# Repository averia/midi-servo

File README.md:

# midi-servo
arduino with midi in-thru-out to move servomotors

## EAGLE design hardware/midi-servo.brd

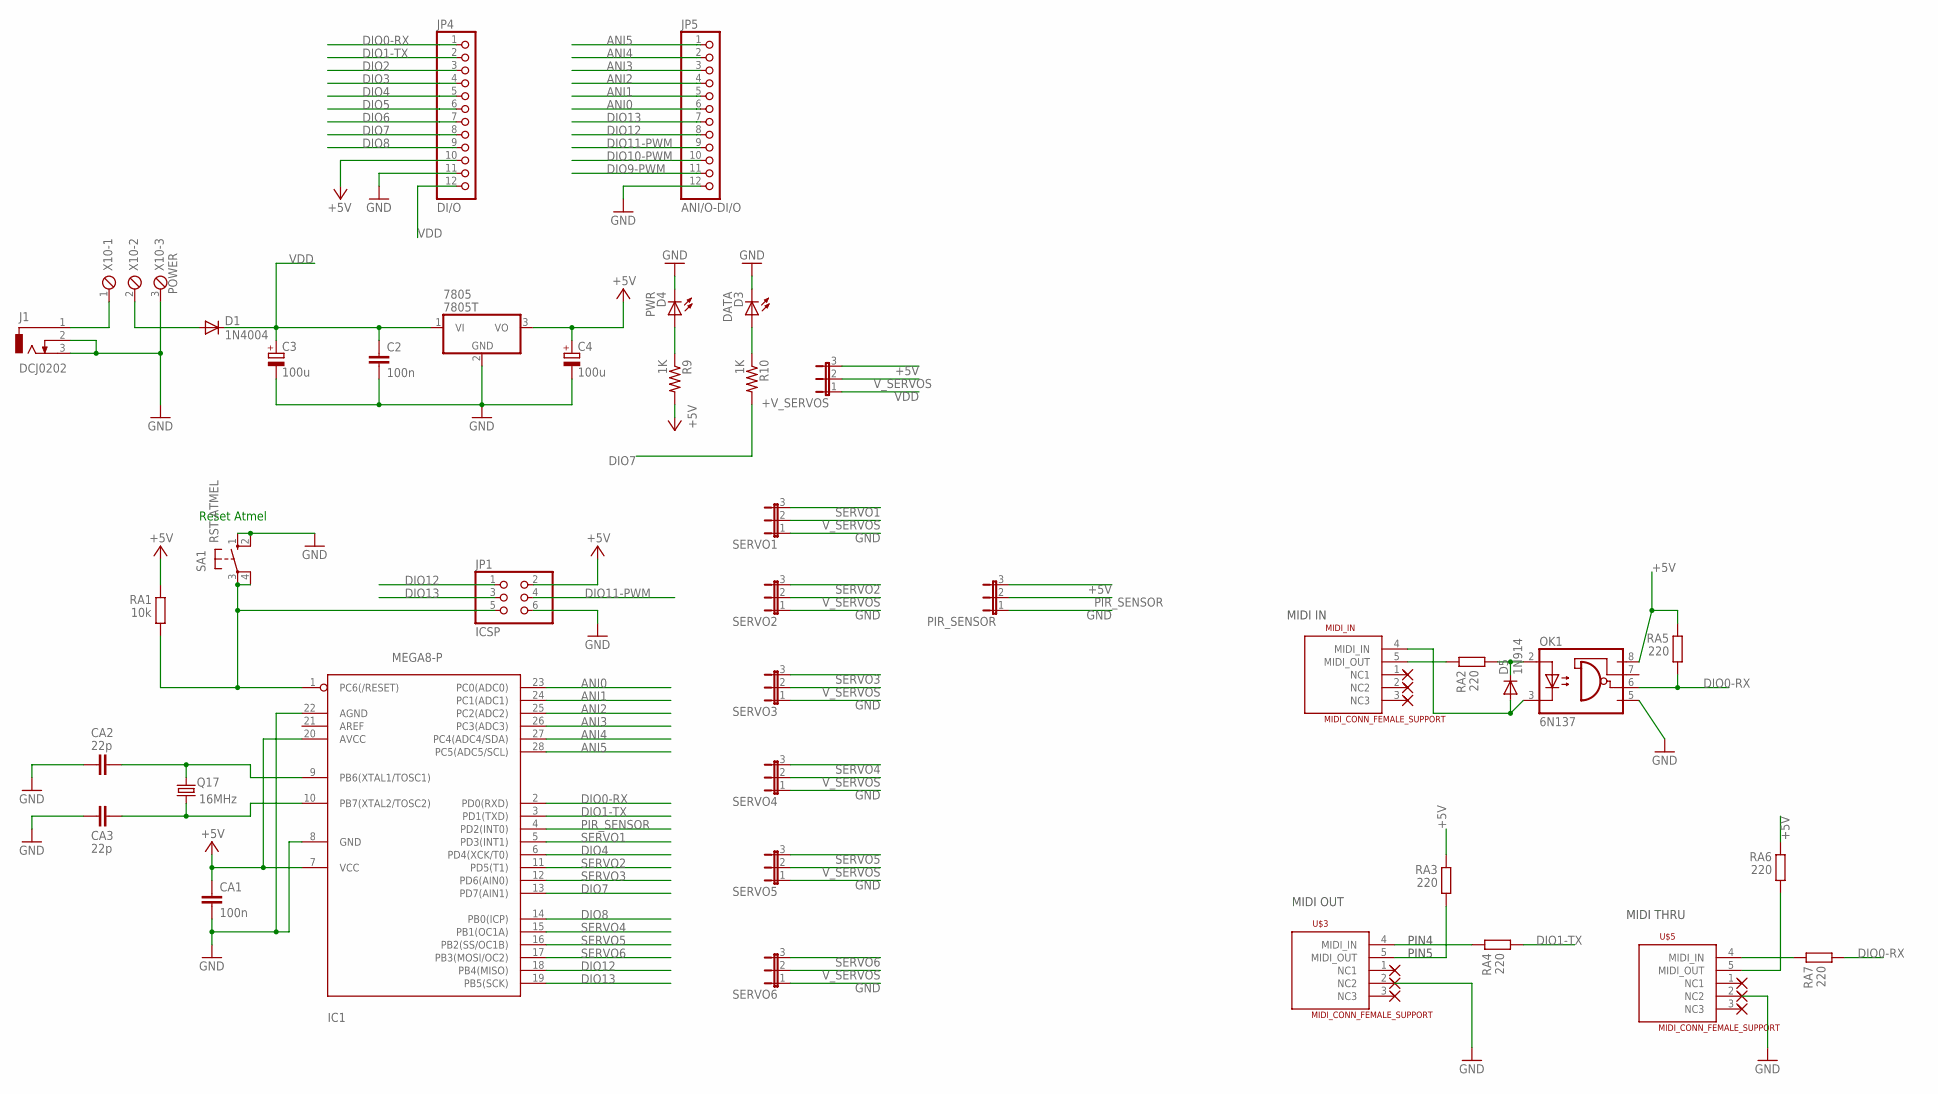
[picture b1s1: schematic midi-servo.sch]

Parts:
7805: 7805T; TO220H
+V_SERVOS: JP2E; JP2
C2: 100n; C050-025X075
C3, C4: 100u; E2,5-7
CA1: 100n; C050-025X075
CA2, CA3: 22p; C050-025X075
D1: 1N4004; DO41-10
D3: DATA; LED4MM
D4: PWR; LED4MM
D5: 1N914; DO34-7
IC1: MEGA8-P; DIL28-3
J1: DCJ0202
JP1: ICSP; 2X03
JP4: DI/O; 1X12
JP5: ANI/O-DI/O; 1X12
MIDI_IN: MIDI_CONN_FEMALE_SUPPORT; DIN_5_FEMALE_SUPPORT
OK1: 6N137; DIL08
PIR_SENSOR: JP2E; JP2
Q17: 16MHz; HC49/S
R9, R10: 1K; 0204/5
RA1: 10k; 0204/5
RA2, RA3, RA4, RA5, RA6, RA7: 220; 0204/5
SA1: RST-ATMEL; B3F-10XX
SERVO1, SERVO2, SERVO3, SERVO4, SERVO5, SERVO6: JP2E; JP2
U$3, U$5: MIDI_CONN_FEMALE_SUPPORT; DIN_5_FEMALE_SUPPORT
X10: POWER; 3POL254

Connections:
56: D5.C, OK1.2 (A), RA2.2
1235: RA3.2, U$3.5 (MIDI_OUT)
+5V: 7805.3 (VO), +V_SERVOS.3, C4.+, CA1.1, IC1.7 (VCC), IC1.20 (AVCC), JP1.2, JP4.10, OK1.8 (VCC), PIR_SENSOR.3, R9.2, RA1.1, RA3.1, RA5.1, RA6.1
ANI0: IC1.23 (PC0(ADC0)), JP5.6
ANI1: IC1.24 (PC1(ADC1)), JP5.5
ANI2: IC1.25 (PC2(ADC2)), JP5.4
ANI3: IC1.26 (PC3(ADC3)), JP5.3
ANI4: IC1.27 (PC4(ADC4/SDA)), JP5.2
ANI5: IC1.28 (PC5(ADC5/SCL)), JP5.1
DIO0-RX: IC1.2 (PD0(RXD)), JP4.1, OK1.6 (VO), RA5.2, RA7.2
DIO1-TX: IC1.3 (PD1(TXD)), JP4.2, RA4.2
DIO2: JP4.3
DIO3: JP4.4
DIO4: IC1.6 (PD4(XCK/T0)), JP4.5
DIO5: JP4.6
DIO6: JP4.7
DIO7: IC1.13 (PD7(AIN1)), JP4.8, R10.2
DIO8: IC1.14 (PB0(ICP)), JP4.9
DIO9-PWM: JP5.11
DIO10-PWM: JP5.10
DIO11-PWM: JP1.4, JP5.9
DIO12: IC1.18 (PB4(MISO)), JP1.1, JP5.8
DIO13: IC1.19 (PB5(SCK)), JP1.3, JP5.7
GND: 7805.2 (GND), C2.2, C3.-, C4.-, CA1.2, CA2.2, CA3.2, D3.A (C), D4.A (C), IC1.8 (GND), IC1.22 (AGND), J1.2, J1.3, JP1.6, JP4.11, JP5.12, OK1.5 (GND), PIR_SENSOR.1, SA1.1 (S), SA1.2 (S1), SERVO1.1, SERVO2.1, SERVO3.1, SERVO4.1, SERVO5.1, SERVO6.1, U$3.2 (NC2), U$5.2 (NC2), X10.3
unnamed: J1.1, X10.1
unnamed: IC1.1 (PC6(/RESET)), JP1.5, RA1.2, SA1.3, SA1.4 (P1)
unnamed: D1.A, X10.2
unnamed: CA2.1, IC1.9 (PB6(XTAL1/TOSC1)), Q17.2
unnamed: CA3.1, IC1.10 (PB7(XTAL2/TOSC2)), Q17.1
unnamed: RA4.1, U$3.4 (MIDI_IN)
unnamed: RA6.2, U$5.5 (MIDI_OUT)
unnamed: RA7.1, U$5.4 (MIDI_IN)
unnamed: MIDI_IN.5 (MIDI_OUT), RA2.1
unnamed: D3.K (A), R10.1
unnamed: D4.K (A), R9.1
PIN5: D5.A, MIDI_IN.4 (MIDI_IN), OK1.3 (C)
PIR_SENSOR: IC1.4 (PD2(INT0)), PIR_SENSOR.2
SERVO1: IC1.5 (PD3(INT1)), SERVO1.3
SERVO2: IC1.11 (PD5(T1)), SERVO2.3
SERVO3: IC1.12 (PD6(AIN0)), SERVO3.3
SERVO4: IC1.15 (PB1(OC1A)), SERVO4.3
SERVO5: IC1.16 (PB2(SS/OC1B)), SERVO5.3
SERVO6: IC1.17 (PB3(MOSI/OC2)), SERVO6.3
VDD: 7805.1 (VI), +V_SERVOS.1, C2.1, C3.+, D1.C, JP4.12
V_SERVOS: +V_SERVOS.2, SERVO1.2, SERVO2.2, SERVO3.2, SERVO4.2, SERVO5.2, SERVO6.2

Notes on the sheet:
Reset Atmel
PIN4
PIN5
MIDI IN
MIDI OUT
MIDI THRU

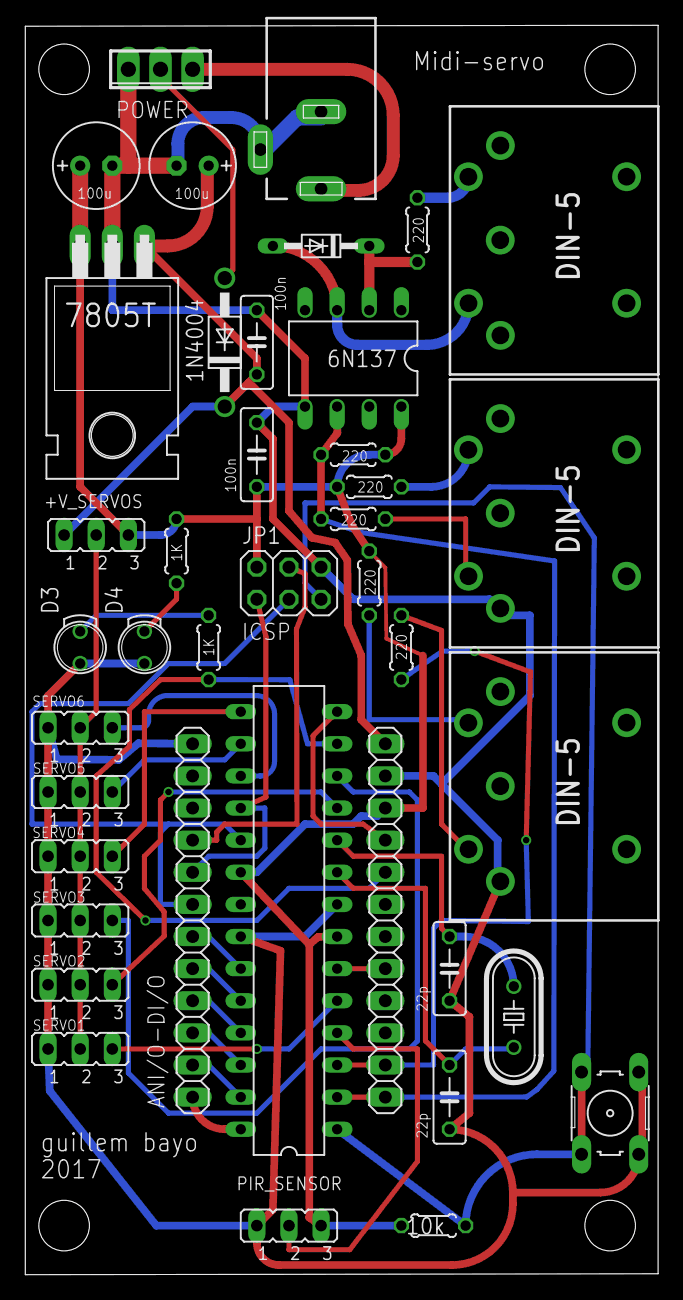
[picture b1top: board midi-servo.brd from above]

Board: 4 copper layers, 50.0 x 98.8 mm, 40 parts (0 on the bottom side), 39 nets.
